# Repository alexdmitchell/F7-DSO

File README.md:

# F7-DSO
DSO Project using the STM 32F746G Discovery Board - custom firmware and analogue front end PCB for my MSc project

Project template & initialisation code generated using STMCubeMX

IDE: Keil uVision 5 Professional

Graticule is displayed in a seperate LCD layer, converted from a JPEG image (drawn in AutoCAD) to c header file using the LCD Image Converter tool: http://www.riuson.com/lcd-image-converter

Features:

2.4 MS/s sampling rate achieved using the onboard ADC (ADC3) and DMA

8 bit resolution

Waveform displayed on the integrated LCD

Full touch screen control

Analogue front end PCB including relay switched 1:1/1:10 attenuation & AC/DC Coupling, Programmable Gain Amplifier with DAC for offset
        
Notes:

You will first need to regenerate the project files using CubeMX (to replace the multiple files in STCubeGenerated that were deleted to reduce file count); open STCubeGenerated.ioc and regenerate the project. Then open the project in uVision and recompile - note that the Pro licence is needed as the code is >32kB.

The input for ADC3 is PA2 on the Arduino header on the rear of the board - the full schematic (EAGLE) for the complete analogue front end PCB is included.

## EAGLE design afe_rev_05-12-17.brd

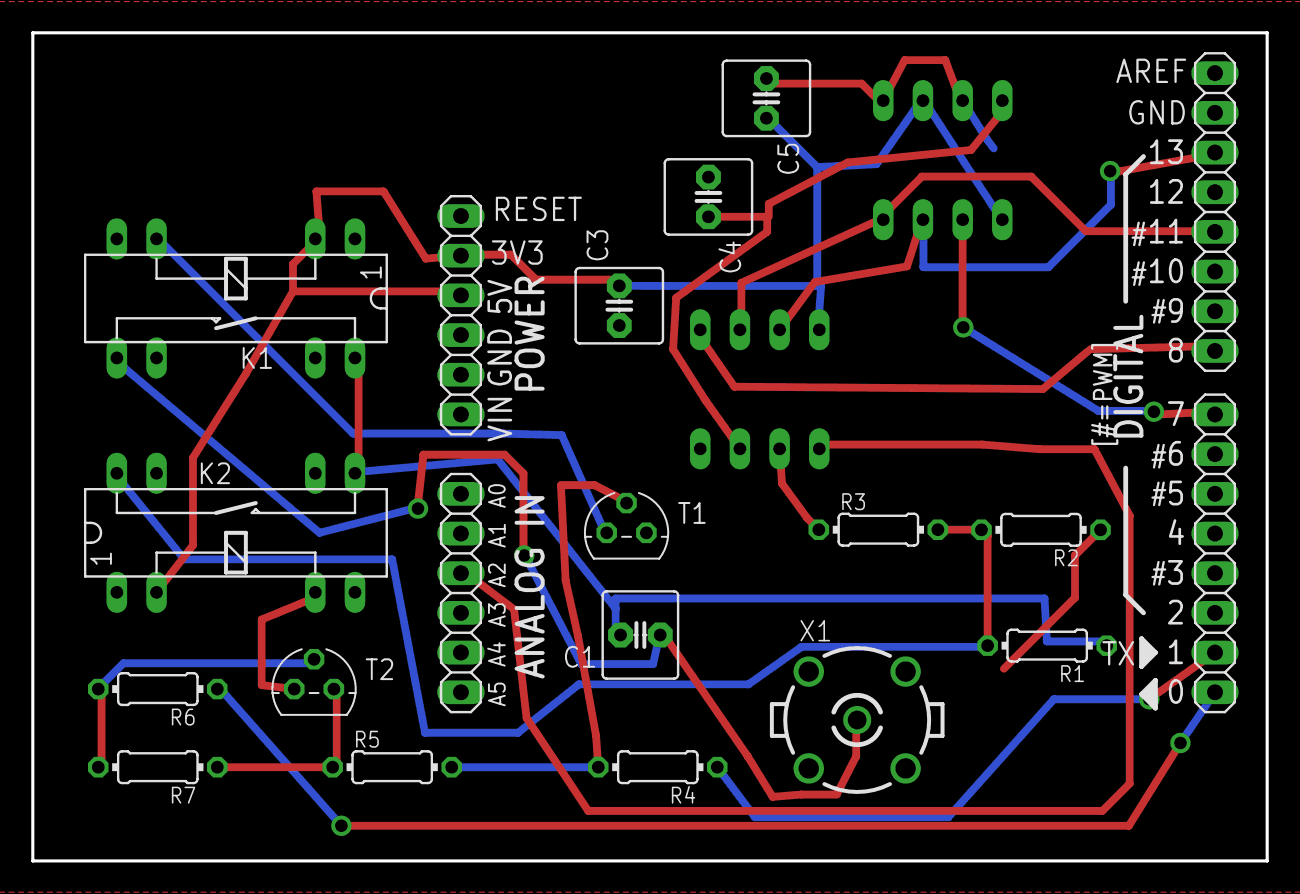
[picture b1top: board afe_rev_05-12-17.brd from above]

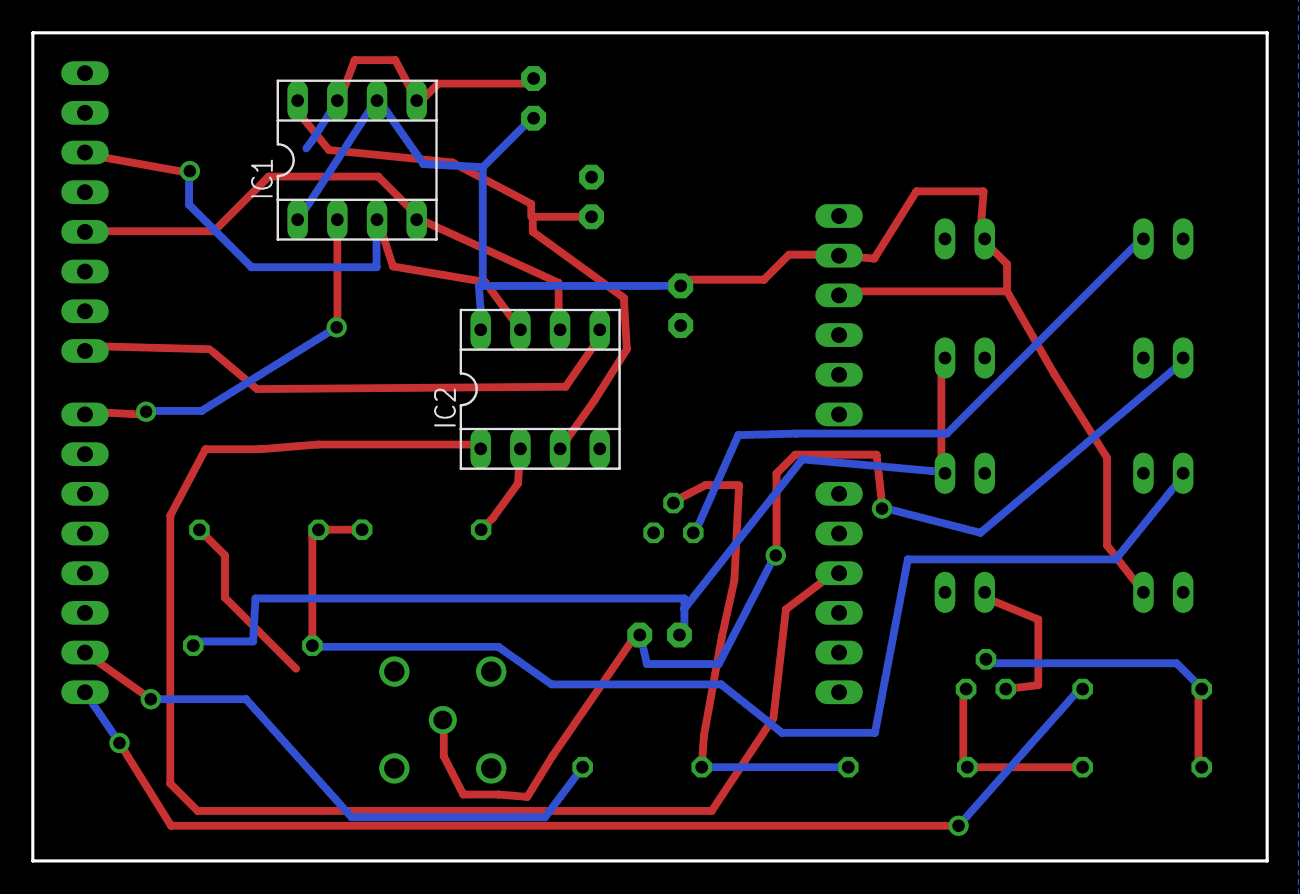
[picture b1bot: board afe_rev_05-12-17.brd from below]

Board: 2 copper layers, 79.0 x 53.0 mm, 22 parts (2 on the bottom side), 18 nets.

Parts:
AD: 1X06
C1, C3, C4, C5: 100n; C2.5-6
IC1, IC2: SOCKET-08
IOH: 1X08
IOL: 1X08
K1, K2: HE751
POWER: 1X06
R1: 9.1M; 0204/7
R2: 1M; 0204/7
R3: 27k; 0204/7
R4, R6: 1k; 0204/7
R5, R7: 10k; 0204/7
T1, T2: BC337; TO92
X1: BN35N61; B35N61

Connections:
5V: K1.2, K2.2, POWER.3
AC_DC: C1.1, K1.8, X1.1
CH0: IC2.2, R3.1
CS2: IC2.5, IOH.1
GND: C3.1, C4.1, C5.1, IC1.5, IC1.7, IC2.4, POWER.5, R2.1, R5.1, R7.1, T1.1, T2.1, X1.2, X1.3, X1.4, X1.5
MOSI: IC1.4, IC2.6, IOH.4
unnamed: K1.6, T1.3
unnamed: R4.2, R5.2
unnamed: R6.2, R7.2, T2.2
unnamed: K2.6, T2.3
unnamed: IOL.1, R6.1
unnamed: IOL.2, R4.1
unnamed: K2.14, R1.2, R2.2, R3.2
SCLK: IC1.3, IC2.7, IOH.6
VDD: C3.2, C5.2, IC1.1, IC1.6, IC2.8, POWER.2
VOUT: AD.3, IC2.1
VOUT-VREF: C4.2, IC2.3
X1_X10: C1.2, K1.14, K2.8, R1.1
